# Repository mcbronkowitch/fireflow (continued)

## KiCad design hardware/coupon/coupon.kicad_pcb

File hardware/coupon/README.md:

# The FireFlow test coupon

A 100 x 80 mm, 4-layer board built around one **Daisy Patch Submodule**, whose
sole job is answering the eight measurement points the M6 hardware envelope
spec puts before panel layout can start —
[`docs/superpowers/specs/2026-08-08-fireflow-hardware-envelope-design.md`](../../docs/superpowers/specs/2026-08-08-fireflow-hardware-envelope-design.md)
§5, addendum 2026-08-30 — chief among them the ADC mux settle time
(`docs/hardware/settle-budget.md`'s prediction, confirmed here rather than on
a breadboard, because the model is linear in node capacitance and a
breadboard's jumper-wire capacitance has no defined value). It is not a
prototype of the instrument: both mux chip footprints, an unpopulated `COM`
capacitor pad, a probe point on `COM`, two pot values side by side, hard-tied
rail neighbours, fixed-divider reference channels, the real 74HC595/74HC165
chain, and the supply topology as a switchable 0R link are the whole circuit.
The full layout act — placement, zone plan, routing — and its reasoning live
in [`docs/superpowers/specs/2026-08-31-coupon-layout-design.md`](../../docs/superpowers/specs/2026-08-31-coupon-layout-design.md).

## Building it

Two generators, run in order, each under a different interpreter:

```
"C:\Users\bernd\AppData\Local\Programs\KiCad\10.0\bin\python.exe" scripts\build.py
"C:\Users\bernd\AppData\Local\Programs\KiCad\10.0\bin\python.exe" scripts\build_pcb.py
```

Both need KiCad's own Python (`pcbnew` is not on the system interpreter's
path) — `build.py` first, because `build_pcb.py` places parts from
`netlist.build()`, the same intent `build.py`'s own proof chain already
checked against the exported schematic netlist. `build.py` writes
`coupon.kicad_sch`, the ERC report and the schematic PDF; `build_pcb.py`
writes `coupon.kicad_pcb` and runs ten proof steps in order, aborting on the
first red one — net comparison, courtyard/shadow placement sanity, plane
connectivity, stitch-copper hygiene, ratsnest, the five analog rules of the
layout spec's Section 4, a final DRC pass (`proof/drc.rpt`), and render +
Gerber/drill export. `scripts/review.py` (same interpreter, once
`build_pcb.py` has written a board — Section 6 of its output reads
`coupon.kicad_pcb` through `check_layout.py`) writes `proof/review.md`, the
sheet meant for actually reading: requirements, channel plan, the Eurorack
connector, BOM, known ERC violations, and the layout section — placement
table, the four numeric analog-rule measurements, and the two families of
measured-but-not-gated deviations (the long 0R ties and the moat-crossing
address bus, both below).

## Stuffing it

`scripts/assembly_plan.py` draws the sheet you actually solder from, because
the fabricated board cannot be read: 0805 parts sit on a 2 mm pitch and their
reference designators need about 5 mm, so the silkscreen overlaps itself and
the analog corner is one grey smear. The board renders under `proof/` have the
same problem for the same reason.

```
python scripts\assembly_plan.py
```

**This one runs under the system interpreter** — it reads `coupon.kicad_pcb`
and nothing else, so no `pcbnew`, no symbol libraries, no KiCad install. Every
number in it is read rather than transcribed: placement, rotation, courtyard
and pad positions come from the footprints, and the part values come from each
footprint's own `Value` property — the same field the BOM in `proof/review.md`
reports. Re-run it after any placement change and the drawing follows; there is
no hand-kept table to drift.

It writes two sheets:

- **`proof/coupon-assembly.svg`** — the working sheet. The whole board, the
  analog corner enlarged, and a stuffing list with one row per reel. All 78
  parts named, coloured by value, with pad 1 marked at its measured position
  (the notch end on the SOIC chips) and a bar on each LED's `_K` pad.
- **`proof/coupon-overview.svg`** — the same geometry at a width that survives
  a narrow column, with eight numbered zones instead of 78 labels. This is the
  one the journal prints, with the assembly sheet linked beside it.

Labels are placed by search, and the script checks its own work: a slot is
rejected if it touches a part body, another label, a leader already drawn or
the board outline, and a leader may not cross a part unless nothing legal is
left. It prints how many labels needed that fallback (one, as of this writing)
and exits non-zero if any part ends up unlabelled or any two labels overlap.

The website keeps its own copies under different names:

```
python scripts\assembly_plan.py --out-dir ..\..\..\FireFlow_Website\public\media\site --prefix fireflow-hw-coupon
```

**`coupon.kicad_pcb` is generated fresh by every `build_pcb.py` run, but the
file is byte-reproducible.** `pcbnew` orders every UUID-keyed item —
footprints, the individual track/via segments sharing a net, and the zone
filler's own bookkeeping — by whatever random UUIDs that run happened to
mint, so an unseeded build reorders on every run even with no source edit
at all (measured, fix-round probe, 2026-09-02: two unseeded builds from the
identical committed source diffed at 26226 lines — `git diff --no-index`,
default context, `| wc -l`; the exact count varies run to run since it
depends on which random UUIDs each pair of builds draws, but it is
reliably five figures).
`hardware/gen/kipcb.py`'s `new_board()` seeds `pcbnew`'s UUID generator with a fixed constant
before creating anything, which makes that whole order reproduce identically
— two from-scratch builds under the same seed produced a 0-diff
`coupon.kicad_pcb`. Regenerating and committing the file is therefore safe
and expected; a real content change is the only thing that should still show
up in `git diff`.

**Every other generated file still shows as modified after each run — that
is expected, and it is timestamps only.** All 32 of them (every gerber,
`coupon.drl`, both board PNGs, `drc.rpt` and `drc-placement.rpt`) embed a
`CreationDate`/wall-clock line KiCad regenerates on every export; the
content underneath is unchanged (confirmed by diffing a gerber with its
`CreationDate`/`Created by ... date` lines excluded: 0 lines differ). Discard
this churn with `git checkout -- hardware/coupon/fab` and, under `proof/`,
every file EXCEPT `review.md` (`coupon-board-front.png`,
`coupon-board-back.png`, `drc.rpt`, `drc-placement.rpt`) — `review.md` is
`review.py`'s own real content, not timestamp noise, and committing it is
the point of that step.

## The two solder jumpers switch one way only

Envelope spec §5 point 8 asks for the supply and ground topology "as a
switchable 0R link, not as a second board variant: the same copy with and
without is the better measurement." **On this board the "without" half of
that does not exist.** `AGND` and `A+3V3` reach the rest of the world
through `JP_GND` and `JP_3V3` and through nothing else — the Eurorack header
grounds pins 3..6 to `GND` (`scripts/netlist.py:139`) and the submodule's A10
feeds `+3V3` (`:97`). Open both jumpers and the analog island is unpowered
and unreferenced; both muxes lose VCC. Point 8 is not met as built, and no
ordering of the measurements recovers it. A second board does not either:
its open state is the same off state.

**What the open state is still good for, and only before the jumpers are
soldered:** meter `TP_AGND` against `TP_GND`, and `TP_A3V3` against
`TP_3V3`. Both must read open. Continuity there means copper crosses the
1.0 mm moat somewhere it should not — a defect in exactly the separation
point 8 is about, and one that is invisible for good once the jumpers are
bridged. A continuity check is an unpowered measurement anyway, so this costs
nothing but the order it is done in.

**Do not power the board with the jumpers open.** It is tempting — the
digital half needs neither of them — but the six address and enable nets run
from `U_SR1` straight into both muxes, whose `VCC` is `A+3V3` and whose `GND`
is `AGND` (`scripts/netlist.py:149`). With `JP_3V3` open that `VCC` floats
while `U_SR1` drives those inputs at 3.3 V, which forward-biases the muxes'
input clamp diodes and powers the chips parasitically through their own
address pins — above the absolute maximum rating of `VCC + 0.5 V`, with
latch-up as the failure mode. The current involved is microamps and it will
very probably survive, but nothing is gained by finding out. Nor can it be
avoided by not running the scan: `~OE` is tied to `GND` and `~SRCLR` to
`+3V3` (`:258`), so the 595 outputs are driven from the instant power is
applied, with whatever the shift register powered up holding. **Meter first,
then bridge both jumpers, then apply power** — in that order, once.

**What does not work is a second join by wire.** The only two places where
both planes are probeable are `TP_AGND` at (10.00, 66.00) and `TP_GND` at
(94.00, 3.00) — 105.0 mm apart, the board's full diagonal. A wire that long
is a component and not a connection, the same trap the `COM` rule below
names.

**A substitute for the lost A/B, neither reviewed nor measured:** change the
link's impedance instead of removing it. A ferrite bead or a small resistor
across `JP_GND`'s pads answers "how good does the single join have to be" at
the designed star point. It costs one rework cycle on a pad, and whether an
0603 lands cleanly on `SolderJumper-2_P1.3mm_Open_Pad1.0x1.5mm`'s 1.3 mm
pitch is unchecked.

**Struck 2026-09-28: point 2's "capacitor at `COM`" case will not be
measured.** Bastian decided against the capacitor test; `C_COM16`/`C_COM8`
stay unpopulated on every board, and "fit none" (`docs/hardware/settle-budget.md`
§4 finding 1) stays arithmetic. The paragraph below is kept as the record of
what that board would have needed.

**A second board for point 2's "capacitor at `COM`" case need not be fully
stuffed.** It needs the submodule and its sockets, `J_PWR`, the bulk caps,
both jumpers, `U_SR1`/`U_SR2`, one mux, `R_REFA1`/`R_REFA2`, the decoupling
caps and the capacitor under test. No pots, no button, no 165, no LEDs —
LEDs only if the round is chasing noise rather than time, which is the load
they are there for (`scripts/design.py:115`).

## Bringing it up

**First powered board, 2026-09-17.** Everything populated except the seven
pots, both solder jumpers bridged, and every measurement below taken with the
Patch Submodule *out* of its sockets. That is the whole scope of what a
module-less power-up can prove: `+3V3` reaches the board only through the
submodule's A10 (`scripts/netlist.py:97`), so with the module out no chip on
either side of the moat has a supply. A dead board is the expected state here,
not a fault.

**Nothing has to be counted, and no reference designator has to be read off
the silkscreen.** Two signatures identify everything:

- **Which bulk-cap pad is ground.** Probe between a pad of `C_BP12` and a pad
  of `C_BN12`, all four combinations: exactly one reads 0 Ω, and those are the
  two ground pads. The opposite combination is +12 V against -12 V.
- **Which socket pin is which.** With one probe on a ground pad, walk the
  other along bank A's ten pins. Exactly two read 0 Ω (A4, A7 — same column,
  one per row), exactly one reads ~1.6 kΩ (A10, `+3V3`), the rest are open.
  A1 and A5 being open is correct: with no module, ±12 V has no DC path to
  ground at all.

Bank A is the 2×5 group at the lower right of the module outline, beside
`J_PWR`, long axis horizontal. Holding the board component side up with the
pot/jack edge at the bottom and the header to the right: **lower row, right to
left, is A1..A5; upper row, right to left, is A10..A6**, so A1 and A10 share
the column nearest the header. (Pad coordinates: `scripts/placement.py`'s
module docstring, transformed by the 180° placement.)

Measured, in the order taken:

| check | reading | what it proves |
|---|---|---|
| across `C_BP12`, across `C_BN12` | 16–17 MΩ, climbing | no short on either ±12 V rail; nothing but the cap loads them |
| `C_BP12` pad vs `C_BN12` pad, 4 combinations | one at 0 Ω, opposite open | rails separated; identifies both ground pads |
| across `C_B3V3` (`+3V3` vs `GND`) | **1.6 kΩ** | see below |
| same, with `SW1` held down | **1.4 kΩ** | `R_BTN` and the button |
| bank A sweep against ground | A4, A7 at 0 Ω; A10 at 1.6 kΩ; rest open | the pin numbering, without counting |
| A1 vs `J_PWR`'s north pins, A5 vs its south pins | 0 Ω (0.1 Ω probe contact) | the ±12 V copper reaches the module |
| **powered:** A1, A5, A10 against A7 | -12 V, +12 V, **0 V** | polarity, and that nothing feeds `+3V3` |

**The 1.6 kΩ is the single most informative reading on the board, and it is
not a fault.** Three reference dividers sit across the analog rail —
`R_REFA1/A2` 20k, `R_REFC1/C2` 20k, `R_REFB1/B2` **2k** — and in parallel
they predict 1.67 kΩ, with the 1k divider dominating. Pressing `SW1` puts
`R_BTN`'s 10k in parallel and predicts 1.43 kΩ. Both landed. Because the
dividers hang on `A+3V3`/`AGND` while the meter sat on `+3V3`/`GND`, that one
reading also proves **both jumpers conduct** — the current goes out through
`JP_3V3` and back through `JP_GND`.

Two practical notes:

- **Park the black probe in A7, not A4.** Both are ground. A7's neighbours A6
  and A8 are unconnected, so a slipped probe there does nothing; A4's
  neighbour is A5 at +12 V.
- **The bulk caps hold ±12 V for minutes after power-off.** Against their own
  measured 16 MΩ leakage and nothing else, the time constant is about 160 s
  (arithmetic from the measured value, not timed). Meter A1 and A5 down to
  ~0 V before the module goes in, or bleed them through a resistor.

**What was not measured, and cannot be any more:** the moat continuity check
this README asks for above — `TP_AGND` open against `TP_GND`, `TP_A3V3` open
against `TP_3V3`. The jumpers were bridged first, and after that both pairs
read 0 Ω whether the moat is clean or shorted. On this board that answer is
gone for good.

**The seven pots went in the same evening, 2026-09-17** — the RV09 vertical
parts from `order-bom.md`, RV3/RV4/RV7 at 20 k and the other four at 10 k. The
support lugs were slightly too large for the board's slots and were clipped
off; each pot hangs on its three solder joints alone, with no glue under the
body. RV4, the tight position between `JP_GND` and `R_SP11`, clears both
with a visible gap, and its case reads open against GND (checked
2026-09-28, board unpowered). (This README said "still unpopulated" until 2026-09-28; the board had
not been in that state since the 17th.)

With the pots in, the bring-up scan read all seven wipers at **63481…63485**
at the clockwise stop, against 63484…63486 on the rail-tied reference channels
(commit `084d702`'s message; no capture is committed). The counter-clockwise
readings were taken but not recorded. That is a **wiring check, not a
characterisation**: at either stop a pot's source impedance is near zero, so
neither reading says anything about settle time or the wait effect. The
hard case — mid travel, R/4, 2.5 kΩ at 10 k and 5 kΩ at 20 k — was measured
on 2026-09-28 on RV2, RV4 and RV6: [`docs/hardware/pots-measured.md`](../../docs/hardware/pots-measured.md).
For that round the pots were set to mid travel on the bring-up scan, to what
`REF_A` reads there, and not touched until both probe images had run.

## Layer and zone map

4 copper layers, y growing downward from the board's top-left corner:

| layer | carries |
|---|---|
| `F.Cu` | signal routing, both plane nets' stitching vias/tracks |
| `In1.Cu` | ground -- **two filled zones**, `GND` under the digital half of the board and `AGND` under the analog half, joined only at `JP_GND` |
| `In2.Cu` | supply -- **two filled zones**, `+3V3` under digital and `A+3V3` under analog, joined only at `JP_3V3`, sourced from the module's own A10 (+3V3 OUT) |
| `B.Cu` | signal overflow where `F.Cu` is blocked, plus the address/enable bus (see below) |

`±12V` is never a plane -- it runs as short, wide (0.8 mm) point-to-point
track, IDC header -> SM supply pins -> bulk caps, per the layout spec's
Section 3.

The board splits into two domains, full board width each, with a 1.0 mm moat
between them (narrow enough that both solder jumpers' fixed 1.3 mm pad pitch
still straddles it): **digital**, y 1..47.6 mm (the shift-register chain,
LEDs, Eurorack header, bulk caps), and **analog**, y 48.6..79 mm (both
muxes, the pots, reference dividers, the audio jack). This is a horizontal
split, not the left/right one the layout spec's Section 3 describes on
paper -- the Patch Submodule's own pad layout decided it: rotated 180 deg so
its sense pins (A2/A3) and audio pins (B1/B2) face the board's bottom edge,
both analog anchors end up on the module's south side, so analog is
everything below it and digital is everything else. `placement.py`'s module
docstring has the full measured reasoning (probed pad coordinates, why 90/270
deg were never an option).

**Two known deviations are measured, printed by `check_layout.py` and
`review.py`'s Section 6, and deliberately not gated** -- fixing either is a
placement-level rework, not something Task 6 (or any task before an order)
attempts:

- **Six of the eight 0R neighbour ties sit well away from the mux pin they
  carry**, against "directly at the mux pin" of the layout spec's Section 4
  rule 3. The measured spread is a continuum, not a few outliers — only
  `R_LO3` (5.99 mm) and `R_HI1` (8.88 mm) are genuinely at their pin, and
  the three longest (`R_HI3` 20.56 mm, `R_HI4` 22.53 mm, `R_LO4` 22.77 mm)
  are barely further out than `R_HI2` (18.97 mm) and `R_LO2` (20.05 mm).
  Read the table in `proof/review.md`, not a count. The longest three sit
  where they do because the only F.Cu approach within reach also carries the
  8:1 mux's own enable pin, which cannot lose its route.

  **What this is expected to cost — reasoned, not measured.** These ties
  hold the *neighbour* channels at a rail while the measured channel settles
  (`docs/hardware/settle-budget.md` §6). A neighbour tied through 0 R is a
  static node: 22 mm of copper leaves it essentially at the rail, and a node
  held at constant DC is a poor aggressor. Charge injection at the address
  switch decays through the extra trace inductance in nanoseconds, against a
  1.6 µs window. So this is expected to be irrelevant to the experiment the
  coupon exists to run — rule 3 is good hygiene here, not a hard
  requirement. The coupon itself is the instrument that would settle it;
  settle-budget.md §5 names crosstalk as what its model is blindest to.
- **Five of the address/enable bus's six nets cross the moat on the board's
  west edge, 70-74 mm from the star point** `JP_GND`, against Section 3's
  "beside the star point." All six originate at `U_SR1`, which sits in the
  far-west digital column (beside the LEDs) rather than beside `JP_GND` on
  the far east -- the crossing follows the source pin, not a routing choice
  that could have moved it without re-placing `U_SR1`.

The same fix (re-pitching the 8:1's column and its west approach) would
touch both. Nobody has done that work yet.

## Before this board is ordered

**Populate copies, never rework one board** -- the fab ships a handful of
identical boards either way, and any question a stuffed board could answer
by soldering something differently is answered by populating a second copy,
not by reworking the first. **Jumper the digital side freely, but never the
`COM` node or the audio path** -- everywhere else a wire is a connection;
on `COM` or on `AUDIO_OUT_L`/`AUDIO_OUT_R` a wire is a component, and the
whole point of measuring on a board instead of a breadboard is that neither
of those paths carries an unmodelled jumper-wire capacitance.

One thing still needs hands on a real board, and one that used to is now
closed (`docs/roadmap.md`'s M6 section carries the up-to-date status):

1. ~~**The Eurorack bus board**~~ -- **closed 2026-09-02, metered.** This
   was the one connection on the whole board with no part datasheet behind
   it: an IDC 2x5 box header's own drawing is mechanical only, and the
   pinout comes from Doepfer's A-100 standard instead.

   **The standard was read first, and it does answer pins 7/8** -- the
   16-pin ribbon runs in pairs (-12V, GND, GND, GND, +12V, +5V, CV, Gate)
   and the 10-pin connector is its first ten conductors, so 3..8 are all
   `GND` and +5 V starts no earlier than 11/12. `review.py`'s Section 3
   carries the sources. **7/8 stay open regardless**, as insurance against a
   non-standard board rather than against a +5 V that the standard does not
   put there; it costs two ground pins.

   **Then the bench answered the part no document could:** Bastian metered
   the bus board and it follows the standard -- red stripe on `-12V`, `GND`
   on 3..8, `+12V` on 9/10. Polarity was the only failure mode that costs
   the board, and it is confirmed the right way round, so this stops being
   an order blocker. Pins 7/8 stop mattering altogether rather than merely
   reading as expected: they are open here, so whatever the bus carries
   there cannot arrive.

   **The shroud deviates from Doepfer's own advice on purpose.** Doepfer
   recommends against keyed headers on bus boards, because mis-keyed boards
   and cables are common. This board keeps one anyway: a rotated or
   row-shifted plug is +/-12 V into the Patch SM, and the notch is what
   makes that impossible. Its one cost cannot be tested until the board
   exists -- a cable keyed the other way will not seat at all -- so that is
   an assembly-time check, not an order blocker. If the plug does not go in,
   the fault is the key and the answer is a different cable, never a cut-off
   nose.

   **Where the notch actually points, measured from the committed
   `coupon.kicad_pcb` on 2026-09-02** -- so nobody re-measures it: the header
   sits at (88.00, 22.00), rotation 0 deg, its pins running south to
   (90.54, 32.16), so the long axis is north-south. The shroud's outer wall
   is x 84.82..93.72, y 16.90..37.26; its **west** inner wall (x 86.02)
   breaks between y 25.03 and y 29.13, with both break ends running out to
   x 84.82. That gap is the polarising notch: 4.10 mm wide, centred on
   y 27.08, which is the pin-5/6 row and the header's own centre. Pin 1 is
   in the x 88.00 column, the notch side. **So the notch faces west, into
   the board.** That was never a free choice -- the footprint fixes the
   notch against the pin numbering and the numbering comes from the
   netlist; the only free parameter was the rotation, and it is 0 deg.

   **Mechanically this is clear on both sides.** Nothing is placed west of
   the header in the y 17..37 band (the nearest neighbour that way is `SW1`
   at y 8, well north). East of it, `C_BN12`/`C_B3V3`/`C_BP12`/`TP_3V3` sit
   on x 96.5 between the shroud and the board's east edge at x 100, but they
   are flat 0805/testpoint parts passing under a plug that rests on the
   shroud. The ribbon can therefore fold either way: 6.3 mm to the east
   edge, or out over open board to the west.
2. **The Patch Submodule's own land-pattern dimensions** -- vendored from
   Electrosmith's KiCad library
   ([`hardware/lib/README.md`](../lib/README.md)), unproven until a module
   actually seats in a fabricated board.

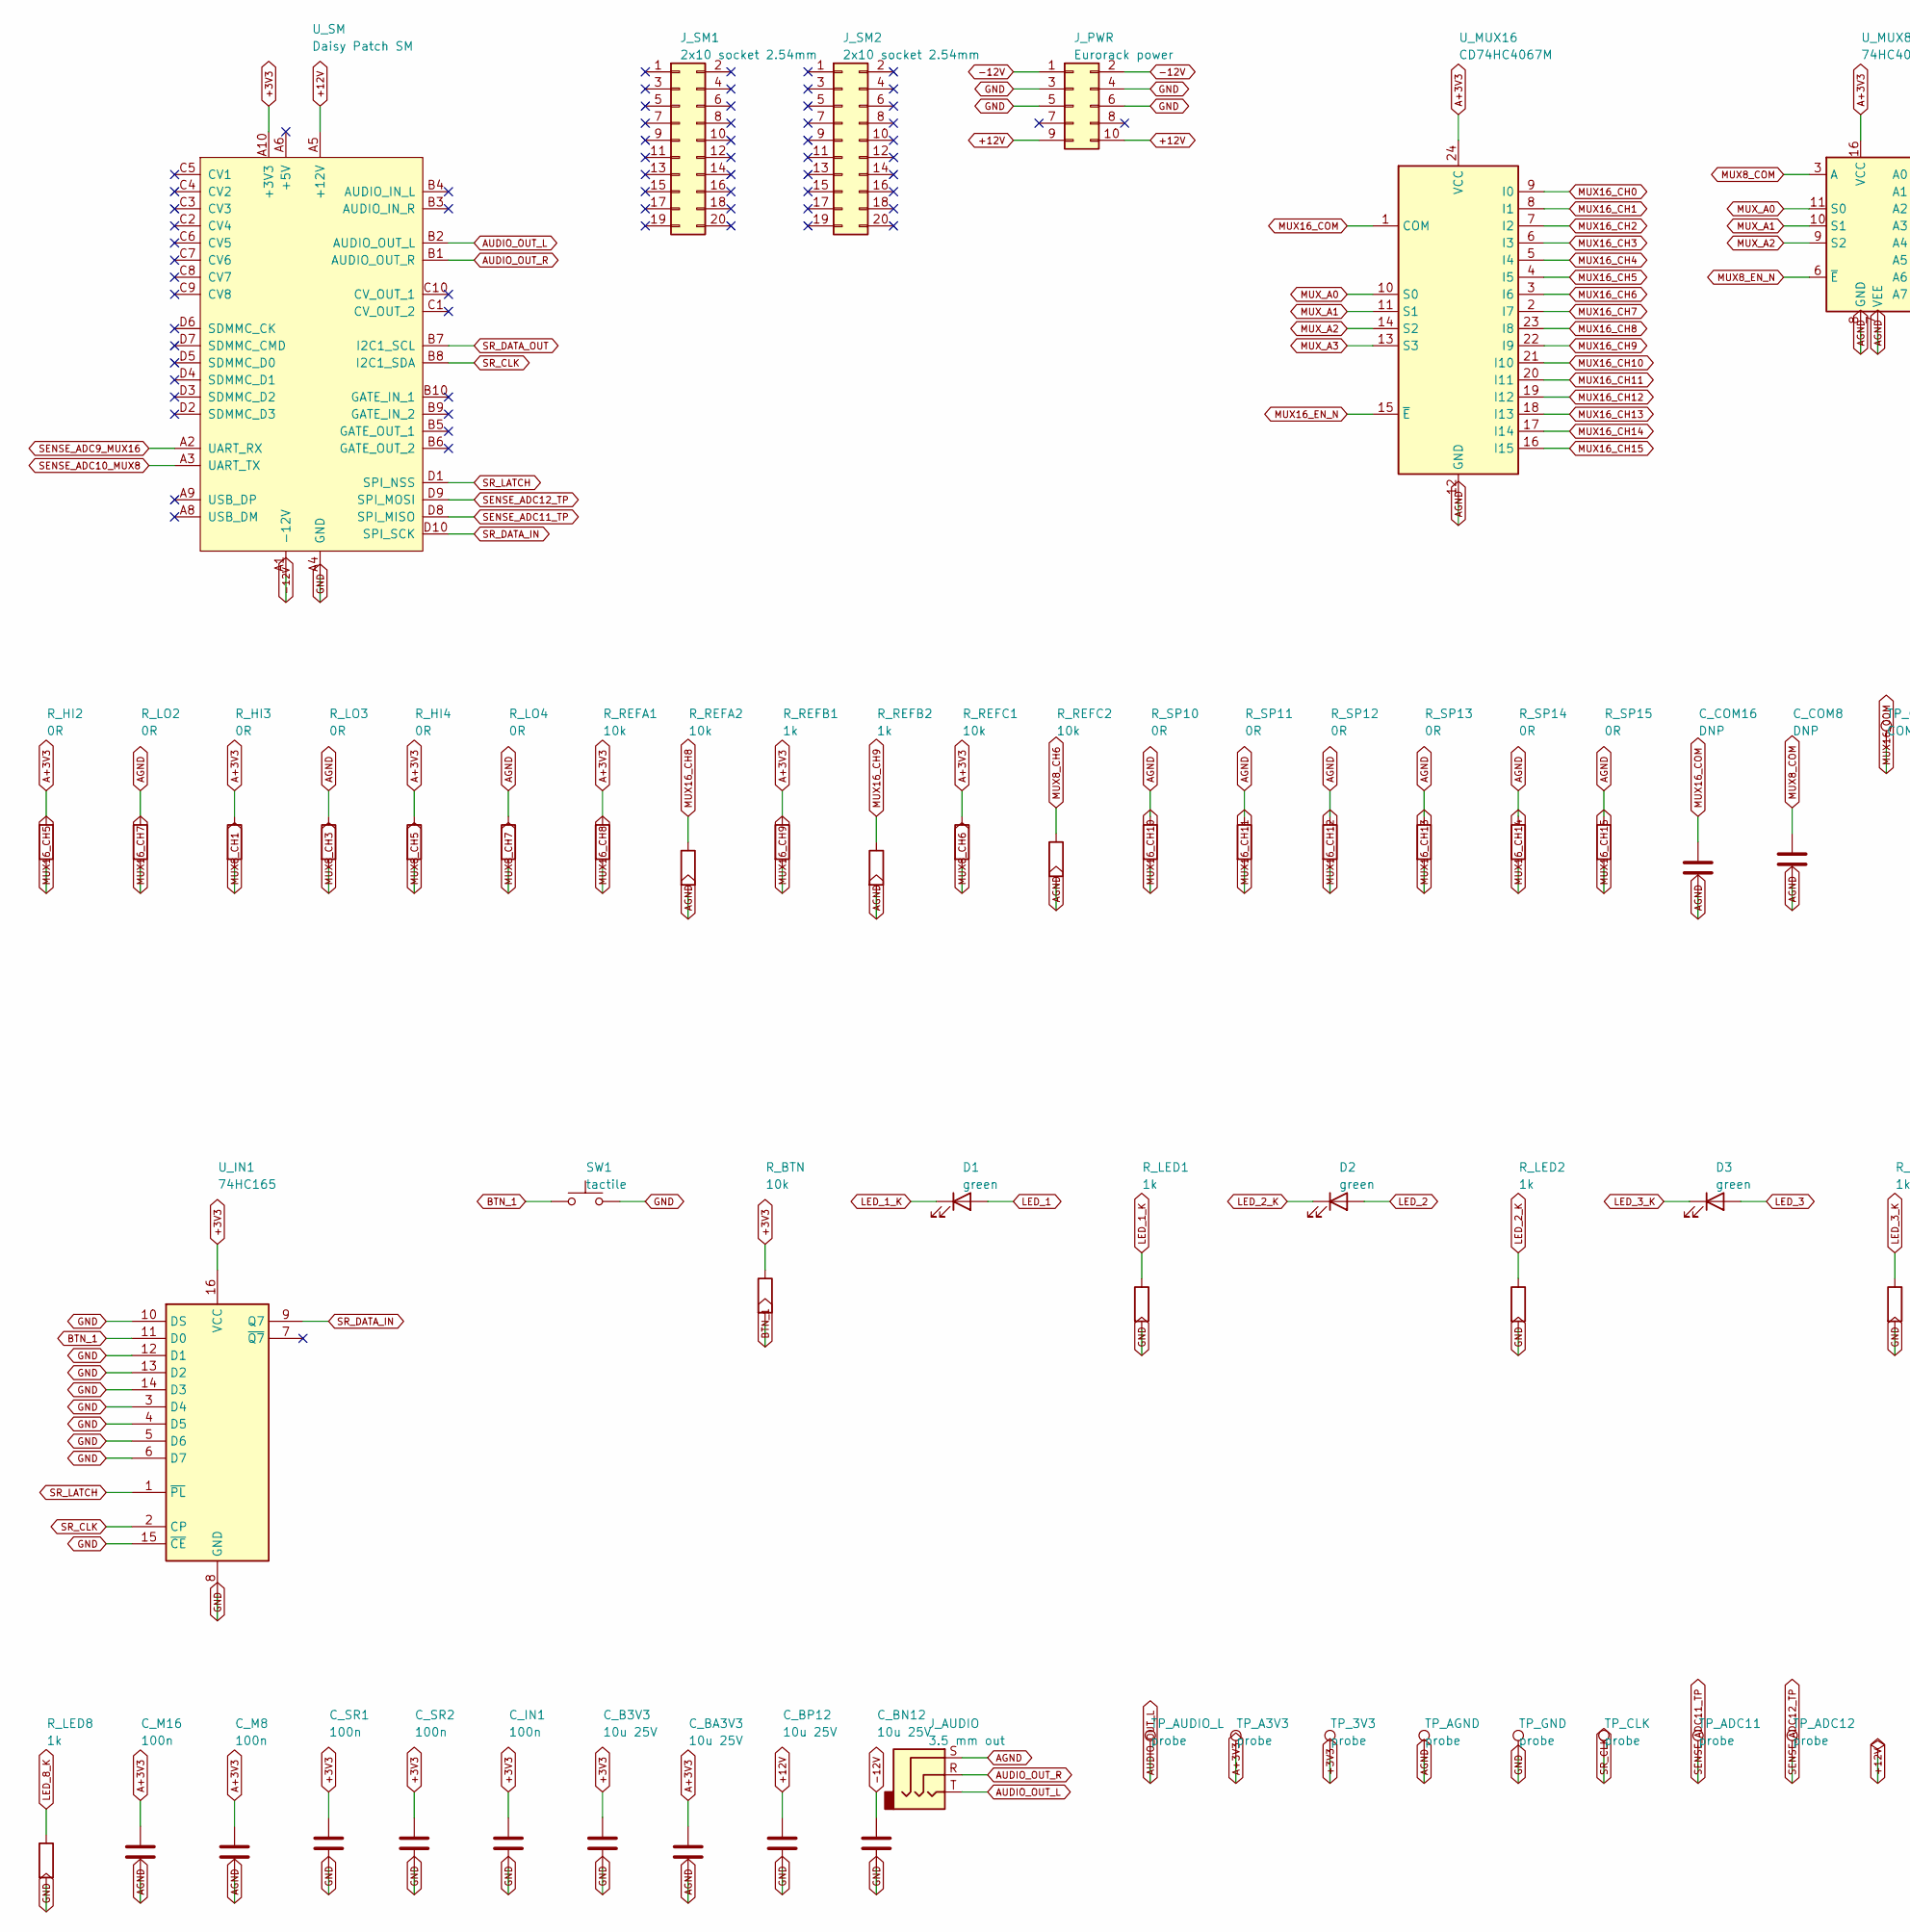
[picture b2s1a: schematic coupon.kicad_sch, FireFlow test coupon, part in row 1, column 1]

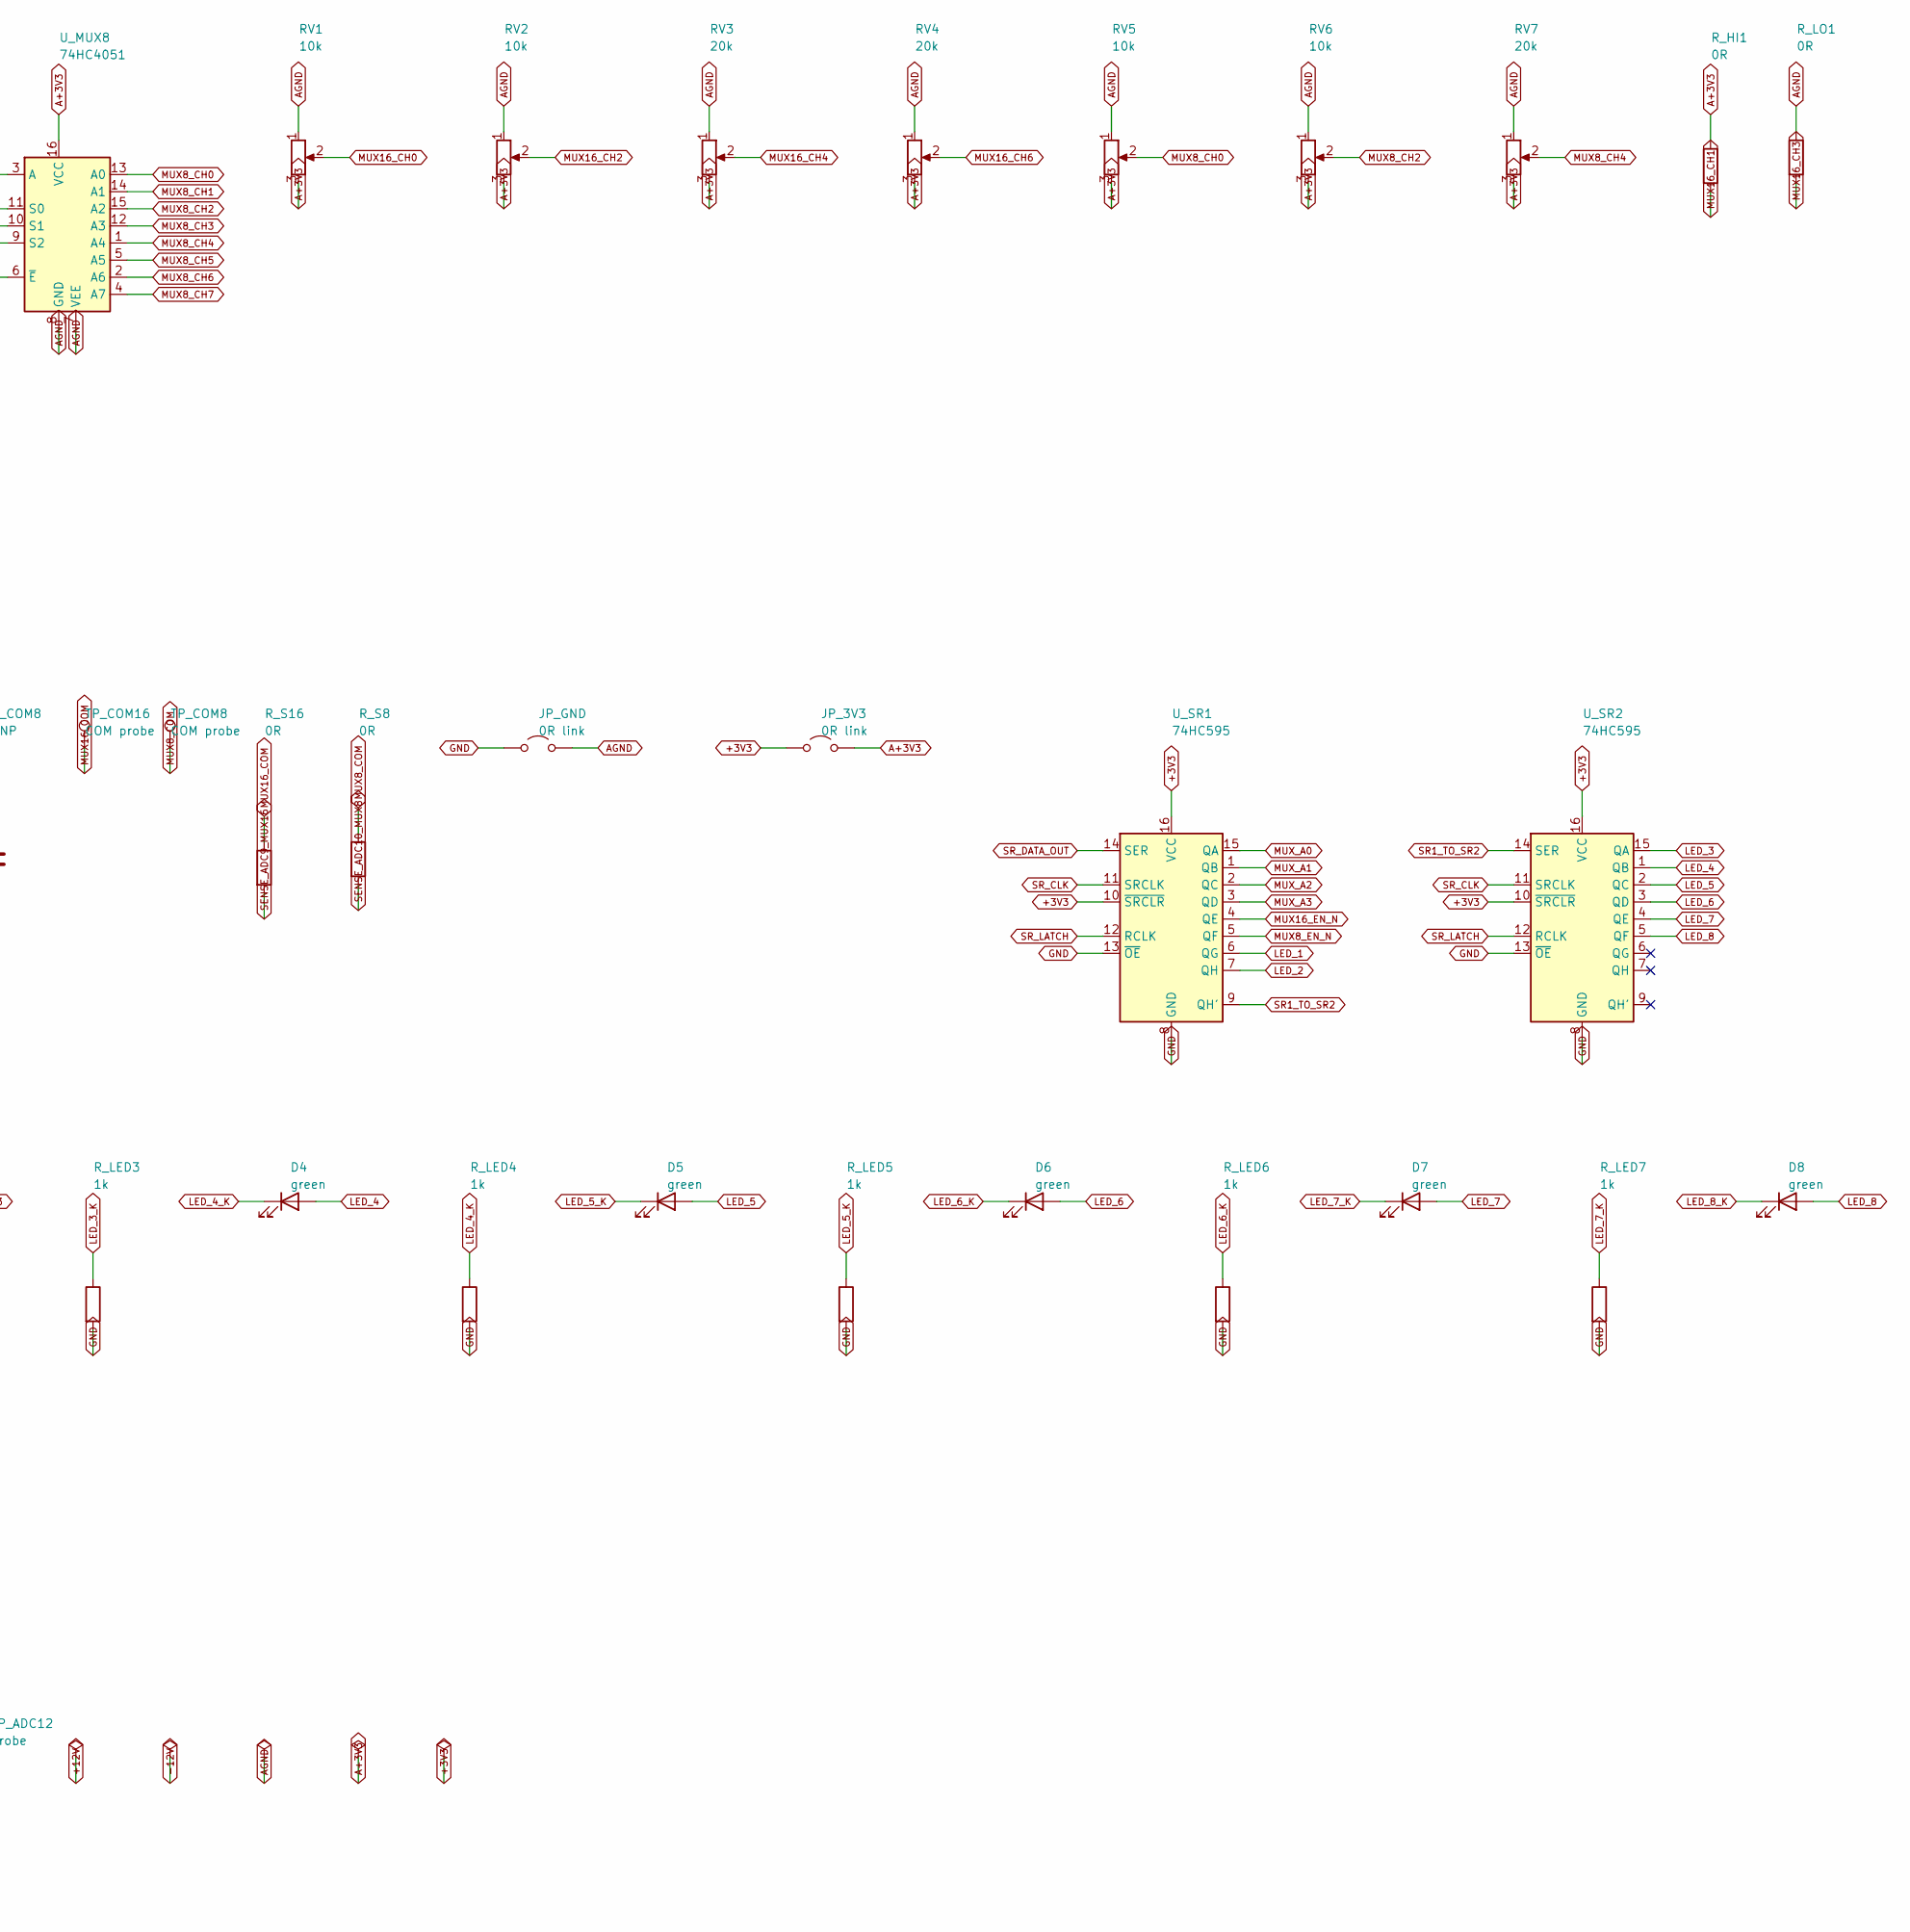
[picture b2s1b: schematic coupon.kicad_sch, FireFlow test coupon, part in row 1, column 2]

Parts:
C_B3V3: 10u 25V; C_0805_2012Metric_Pad1.18x1.45mm_HandSolder
C_BA3V3: 10u 25V; C_0805_2012Metric_Pad1.18x1.45mm_HandSolder
C_BN12: 10u 25V; C_0805_2012Metric_Pad1.18x1.45mm_HandSolder
C_BP12: 10u 25V; C_0805_2012Metric_Pad1.18x1.45mm_HandSolder
C_COM8, C_COM16: DNP; C_0805_2012Metric_Pad1.18x1.45mm_HandSolder
C_IN1: 100n; C_0805_2012Metric_Pad1.18x1.45mm_HandSolder
C_M8, C_M16: 100n; C_0805_2012Metric_Pad1.18x1.45mm_HandSolder
C_SR1, C_SR2: 100n; C_0805_2012Metric_Pad1.18x1.45mm_HandSolder
D1, D2, D3, D4, D5, D6, D7, D8: green; LED_0805_2012Metric_Pad1.15x1.40mm_HandSolder
JP_3V3: 0R link; SolderJumper-2_P1.3mm_Open_Pad1.0x1.5mm
JP_GND: 0R link; SolderJumper-2_P1.3mm_Open_Pad1.0x1.5mm
J_AUDIO: 3.5 mm out; Jack_3.5mm_CUI_SJ1-3513N_Horizontal
J_PWR: Eurorack power; IDC-Header_2x05_P2.54mm_Vertical
J_SM1, J_SM2: 2x10 socket 2.54mm
RV1, RV2, RV5, RV6: 10k; Potentiometer_Alpha_RD901F-40-00D_Single_Vertical
RV3, RV4, RV7: 20k; Potentiometer_Alpha_RD901F-40-00D_Single_Vertical
R_BTN: 10k; R_0805_2012Metric_Pad1.20x1.40mm_HandSolder
R_HI1, R_HI2, R_HI3, R_HI4: 0R; R_0805_2012Metric_Pad1.20x1.40mm_HandSolder
R_LED1, R_LED2, R_LED3, R_LED4, R_LED5, R_LED6, R_LED7, R_LED8: 1k; R_0805_2012Metric_Pad1.20x1.40mm_HandSolder
R_LO1, R_LO2, R_LO3, R_LO4: 0R; R_0805_2012Metric_Pad1.20x1.40mm_HandSolder
R_REFA1, R_REFA2: 10k; R_0805_2012Metric_Pad1.20x1.40mm_HandSolder
R_REFB1, R_REFB2: 1k; R_0805_2012Metric_Pad1.20x1.40mm_HandSolder
R_REFC1, R_REFC2: 10k; R_0805_2012Metric_Pad1.20x1.40mm_HandSolder
R_S8, R_S16: 0R; R_0805_2012Metric_Pad1.20x1.40mm_HandSolder
R_SP10, R_SP11, R_SP12, R_SP13, R_SP14, R_SP15: 0R; R_0805_2012Metric_Pad1.20x1.40mm_HandSolder
SW1: tactile; SW_PUSH_6mm
TP_3V3: probe; TestPoint_Pad_D1.5mm
TP_A3V3: probe; TestPoint_Pad_D1.5mm
TP_ADC11, TP_ADC12: probe; TestPoint_Pad_D1.5mm
TP_AGND: probe; TestPoint_Pad_D1.5mm
TP_AUDIO_L: probe; TestPoint_Pad_D1.5mm
TP_CLK: probe; TestPoint_Pad_D1.5mm
TP_COM8, TP_COM16: COM probe; TestPoint_Pad_D1.5mm
TP_GND: probe; TestPoint_Pad_D1.5mm
U_IN1: 74HC165; SOIC-16_3.9x9.9mm_P1.27mm
U_MUX8: 74HC4051; SOIC-16_3.9x9.9mm_P1.27mm
U_MUX16: CD74HC4067M; SOIC-24W_7.5x15.4mm_P1.27mm
U_SM: Daisy Patch SM; DAISY_PATCH_SM
U_SR1, U_SR2: 74HC595; SOIC-16_3.9x9.9mm_P1.27mm

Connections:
+3V3: C_B3V3.1, C_IN1.1, C_SR1.1, C_SR2.1, JP_3V3.1 (A), R_BTN.1, TP_3V3.1, U_IN1.16 (VCC), U_SM.A10 (+3V3), U_SR1.10 (~SRCLR), U_SR1.16 (VCC), U_SR2.10 (~SRCLR), U_SR2.16 (VCC)
+12V: C_BP12.1, J_PWR.9, J_PWR.10, U_SM.A5 (+12V)
-12V: C_BN12.1, J_PWR.1, J_PWR.2, U_SM.A1 (-12V)
A+3V3: C_BA3V3.1, C_M8.1, C_M16.1, JP_3V3.2 (B), RV1.3, RV2.3, RV3.3, RV4.3, RV5.3, RV6.3, RV7.3, R_HI1.1, R_HI2.1, R_HI3.1, R_HI4.1, R_REFA1.1, R_REFB1.1, R_REFC1.1, TP_A3V3.1, U_MUX8.16 (VCC), U_MUX16.24 (VCC)
AGND: C_BA3V3.2, C_COM8.2, C_COM16.2, C_M8.2, C_M16.2, JP_GND.2 (B), J_AUDIO.S, RV1.1, RV2.1, RV3.1, RV4.1, RV5.1, RV6.1, RV7.1, R_LO1.1, R_LO2.1, R_LO3.1, R_LO4.1, R_REFA2.2, R_REFB2.2, R_REFC2.2, R_SP10.1, R_SP11.1, R_SP12.1, R_SP13.1, R_SP14.1, R_SP15.1, TP_AGND.1, U_MUX8.7 (VEE), U_MUX8.8 (GND), U_MUX16.12 (GND)
AUDIO_OUT_L: J_AUDIO.T, TP_AUDIO_L.1, U_SM.B2 (AUDIO_OUT_L)
AUDIO_OUT_R: J_AUDIO.R, U_SM.B1 (AUDIO_OUT_R)
BTN_1: R_BTN.2, SW1.1, U_IN1.11 (D0)
GND: C_B3V3.2, C_BN12.2, C_BP12.2, C_IN1.2, C_SR1.2, C_SR2.2, JP_GND.1 (A), J_PWR.3, J_PWR.4, J_PWR.5, J_PWR.6, R_LED1.2, R_LED2.2, R_LED3.2, R_LED4.2, R_LED5.2, R_LED6.2, R_LED7.2, R_LED8.2, SW1.2, TP_GND.1, U_IN1.3 (D4), U_IN1.4 (D5), U_IN1.5 (D6), U_IN1.6 (D7), U_IN1.8 (GND), U_IN1.10 (DS), U_IN1.12 (D1), U_IN1.13 (D2), U_IN1.14 (D3), U_IN1.15 (~CE), U_SM.A4 (GND), U_SM.A7 (GND), U_SR1.8 (GND), U_SR1.13 (~OE), U_SR2.8 (GND), U_SR2.13 (~OE)
LED_1: D1.2 (A), U_SR1.6 (QG)
LED_1_K: D1.1 (K), R_LED1.1
LED_2: D2.2 (A), U_SR1.7 (QH)
LED_2_K: D2.1 (K), R_LED2.1
LED_3: D3.2 (A), U_SR2.15 (QA)
LED_3_K: D3.1 (K), R_LED3.1
LED_4: D4.2 (A), U_SR2.1 (QB)
LED_4_K: D4.1 (K), R_LED4.1
LED_5: D5.2 (A), U_SR2.2 (QC)
LED_5_K: D5.1 (K), R_LED5.1
LED_6: D6.2 (A), U_SR2.3 (QD)
LED_6_K: D6.1 (K), R_LED6.1
LED_7: D7.2 (A), U_SR2.4 (QE)
LED_7_K: D7.1 (K), R_LED7.1
LED_8: D8.2 (A), U_SR2.5 (QF)
LED_8_K: D8.1 (K), R_LED8.1
MUX8_CH0: RV5.2, U_MUX8.13 (A0)
MUX8_CH1: R_HI3.2, U_MUX8.14 (A1)
MUX8_CH2: RV6.2, U_MUX8.15 (A2)
MUX8_CH3: R_LO3.2, U_MUX8.12 (A3)
MUX8_CH4: RV7.2, U_MUX8.1 (A4)
MUX8_CH5: R_HI4.2, U_MUX8.5 (A5)
MUX8_CH6: R_REFC1.2, R_REFC2.1, U_MUX8.2 (A6)
MUX8_CH7: R_LO4.2, U_MUX8.4 (A7)
MUX8_COM: C_COM8.1, R_S8.1, TP_COM8.1, U_MUX8.3 (A)
MUX8_EN_N: U_MUX8.6 (~E), U_SR1.5 (QF)
MUX16_CH0: RV1.2, U_MUX16.9 (I0)
MUX16_CH1: R_HI1.2, U_MUX16.8 (I1)
MUX16_CH2: RV2.2, U_MUX16.7 (I2)
MUX16_CH3: R_LO1.2, U_MUX16.6 (I3)
MUX16_CH4: RV3.2, U_MUX16.5 (I4)
MUX16_CH5: R_HI2.2, U_MUX16.4 (I5)
MUX16_CH6: RV4.2, U_MUX16.3 (I6)
MUX16_CH7: R_LO2.2, U_MUX16.2 (I7)
MUX16_CH8: R_REFA1.2, R_REFA2.1, U_MUX16.23 (I8)
MUX16_CH9: R_REFB1.2, R_REFB2.1, U_MUX16.22 (I9)
MUX16_CH10: R_SP10.2, U_MUX16.21 (I10)
MUX16_CH11: R_SP11.2, U_MUX16.20 (I11)
MUX16_CH12: R_SP12.2, U_MUX16.19 (I12)
MUX16_CH13: R_SP13.2, U_MUX16.18 (I13)
MUX16_CH14: R_SP14.2, U_MUX16.17 (I14)
MUX16_CH15: R_SP15.2, U_MUX16.16 (I15)
MUX16_COM: C_COM16.1, R_S16.1, TP_COM16.1, U_MUX16.1 (COM)
MUX16_EN_N: U_MUX16.15 (~E), U_SR1.4 (QE)
MUX_A0: U_MUX8.11 (S0), U_MUX16.10 (S0), U_SR1.15 (QA)
MUX_A1: U_MUX8.10 (S1), U_MUX16.11 (S1), U_SR1.1 (QB)
MUX_A2: U_MUX8.9 (S2), U_MUX16.14 (S2), U_SR1.2 (QC)
MUX_A3: U_MUX16.13 (S3), U_SR1.3 (QD)
SENSE_ADC9_MUX16: R_S16.2, U_SM.A2 (UART_RX)
SENSE_ADC10_MUX8: R_S8.2, U_SM.A3 (UART_TX)
SENSE_ADC11_TP: TP_ADC11.1, U_SM.D8 (SPI_MISO)
SENSE_ADC12_TP: TP_ADC12.1, U_SM.D9 (SPI_MOSI)
SR1_TO_SR2: U_SR1.9 (QH'), U_SR2.14 (SER)
SR_CLK: TP_CLK.1, U_IN1.2 (CP), U_SM.B8 (I2C1_SDA), U_SR1.11 (SRCLK), U_SR2.11 (SRCLK)
SR_DATA_IN: U_IN1.9 (Q7), U_SM.D10 (SPI_SCK)
SR_DATA_OUT: U_SM.B7 (I2C1_SCL), U_SR1.14 (SER)
SR_LATCH: U_IN1.1 (~PL), U_SM.D1 (SPI_NSS), U_SR1.12 (RCLK), U_SR2.12 (RCLK)

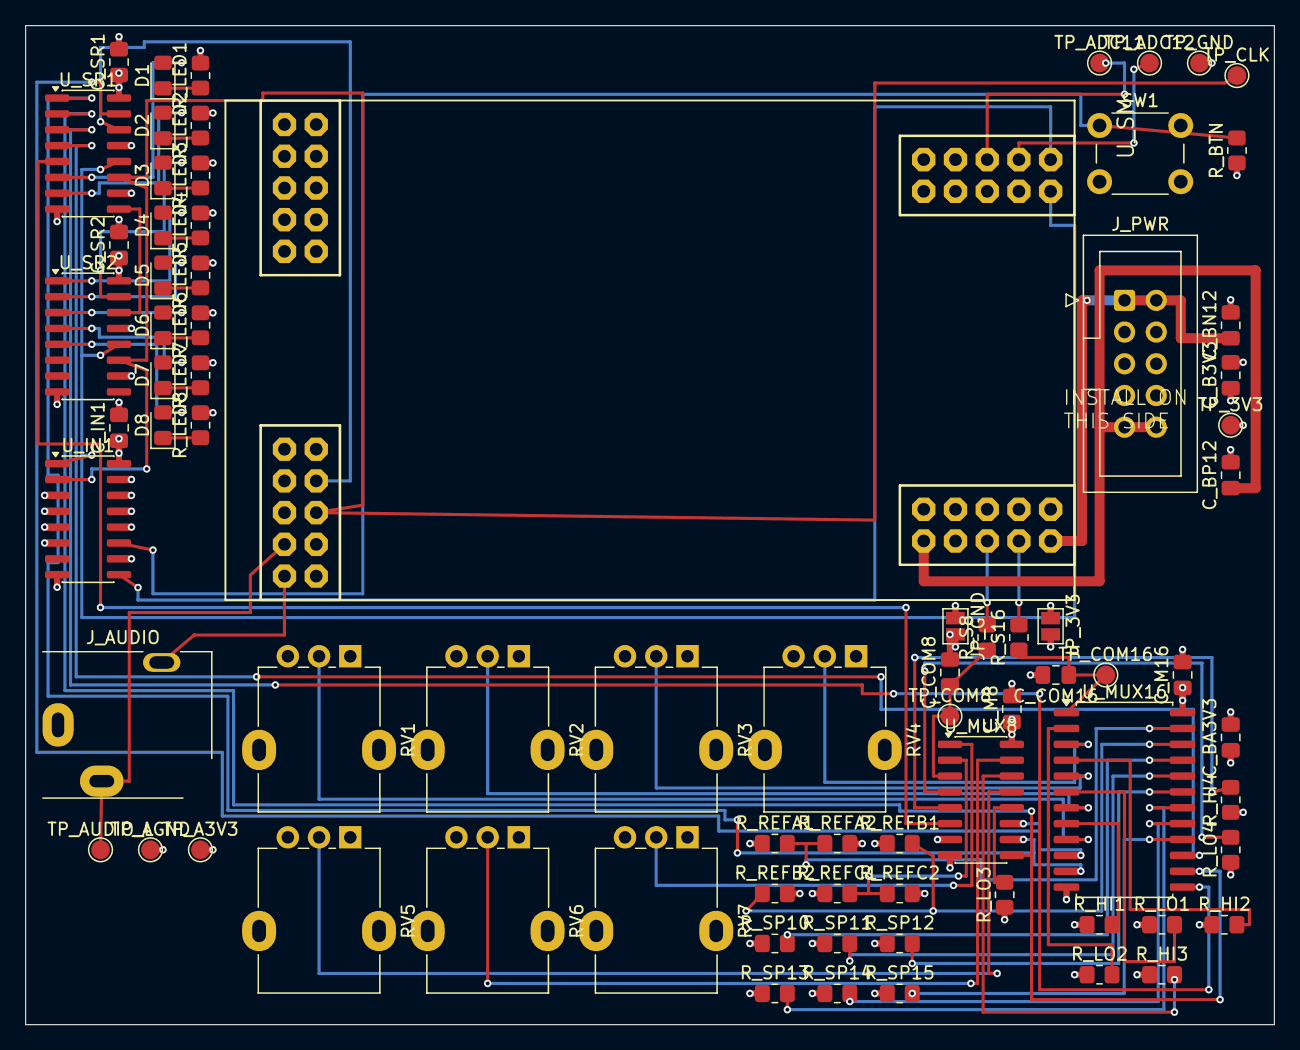
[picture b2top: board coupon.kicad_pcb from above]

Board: 4 copper layers, 100.0 x 80.0 mm, 78 parts (0 on the bottom side), 66 nets.
